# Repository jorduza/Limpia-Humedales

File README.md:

### Link a la wiki para la documentacion del trabajo
https://github.com/jorduza/Limpia-Humedales/wiki/0.-HOME

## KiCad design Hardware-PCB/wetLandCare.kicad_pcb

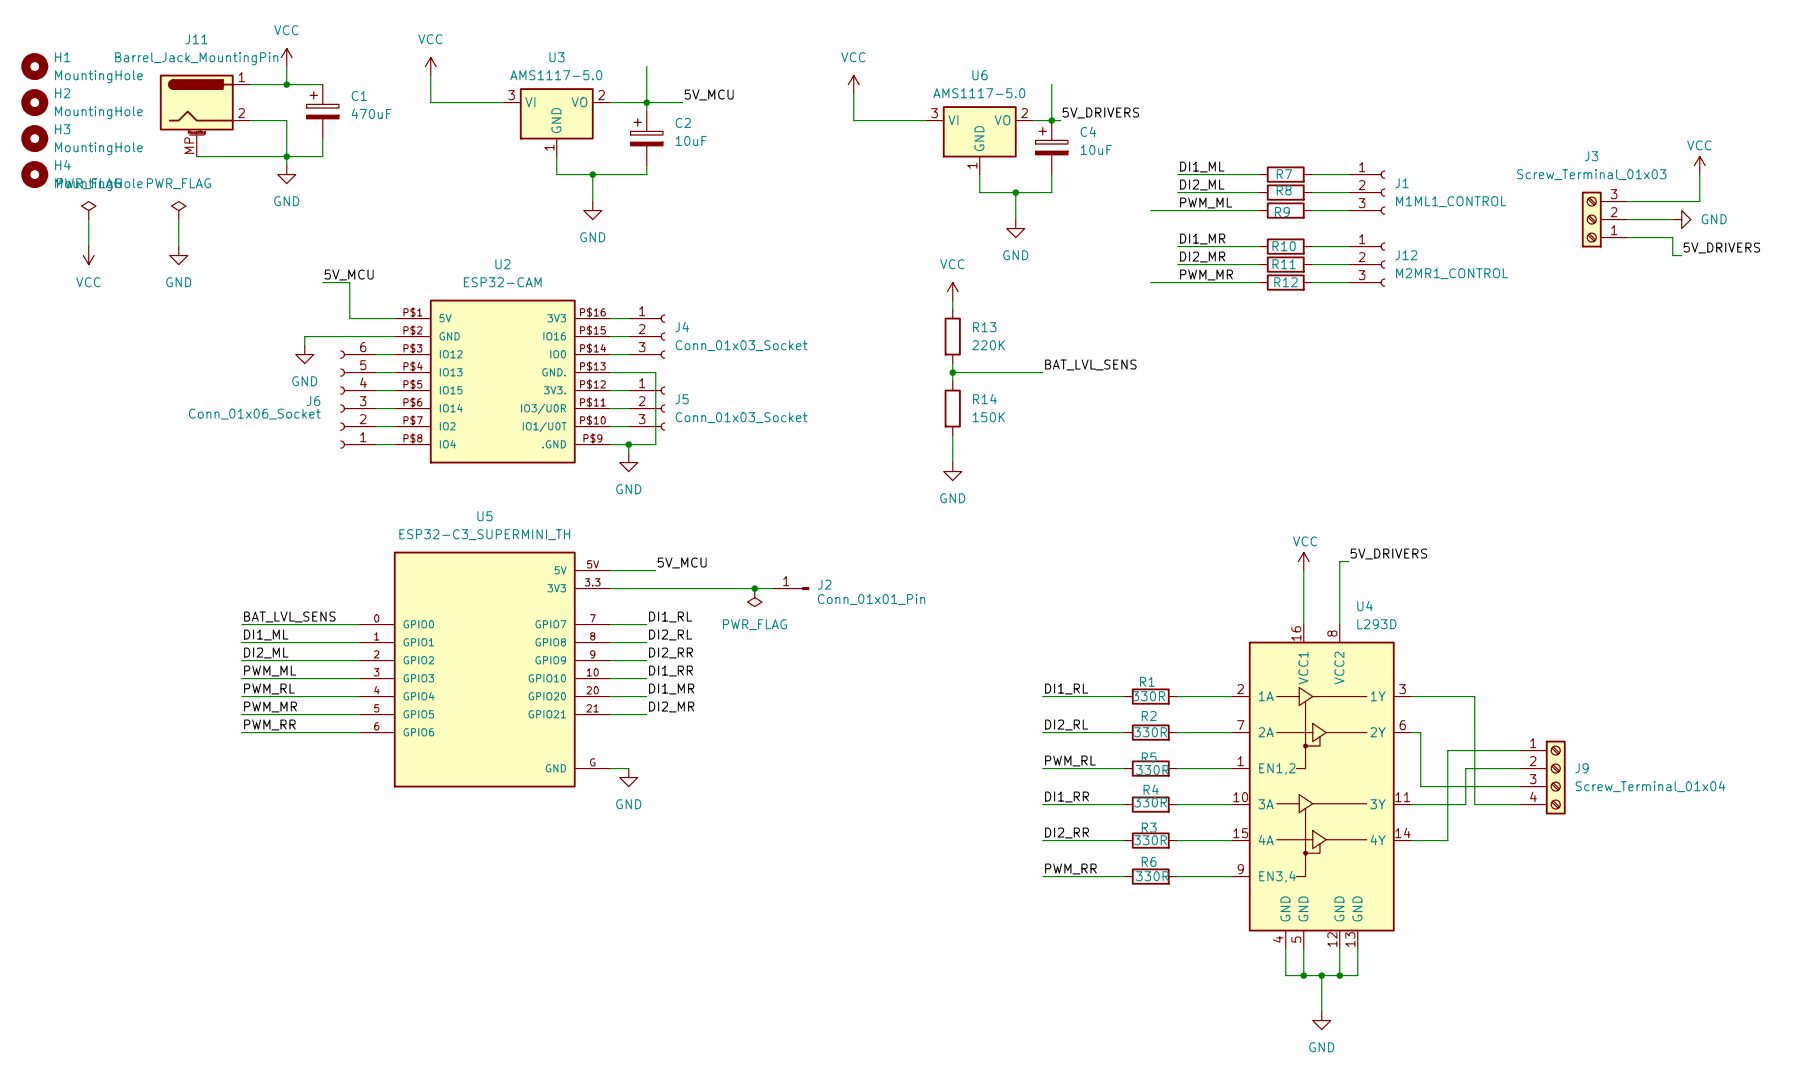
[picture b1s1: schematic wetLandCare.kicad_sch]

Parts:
C1: 470uF; CP_Radial_D8.0mm_P3.80mm
C2, C4: 10uF; CP_Radial_D4.0mm_P2.00mm
H1, H2, H3, H4: MountingHole; MountingHole_3.2mm_M3_DIN965_Pad
J1: M1ML1_CONTROL; PinSocket_1x03_P2.54mm_Vertical
J2: Conn_01x01_Pin; PinSocket_1x01_P2.54mm_Vertical
J3: Screw_Terminal_01x03; TerminalBlock_Altech_AK300-3_P5.00mm
J4, J5: Conn_01x03_Socket; PinSocket_1x03_P2.54mm_Vertical
J6: Conn_01x06_Socket; PinSocket_1x06_P2.54mm_Vertical
J9: Screw_Terminal_01x04; TerminalBlock_Altech_AK300-4_P5.00mm
J11: Barrel_Jack_MountingPin; BarrelJack_Kycon_KLDX-0202-xC_Horizontal
J12: M2MR1_CONTROL; PinSocket_1x03_P2.54mm_Vertical
R1, R2, R3, R4, R5, R6, R7, R8, R9, R10, R11, R12: 330R; R_Axial_DIN0207_L6.3mm_D2.5mm_P7.62mm_Horizontal
R13: 220K; R_Axial_DIN0207_L6.3mm_D2.5mm_P7.62mm_Horizontal
R14: 150K; R_Axial_DIN0207_L6.3mm_D2.5mm_P7.62mm_Horizontal
U2: ESP32-CAM
U3, U6: AMS1117-5.0; SOT-223-3_TabPin2
U4: L293D; DIP-16_W7.62mm
U5: ESP32-C3_SUPERMINI_TH; MODULE_ESP32-C3_SUPERMINI_TH

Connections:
/5V_DRIVERS: C4.1, J3.1, U4.8 (VCC2), U6.2 (VO)
/5V_MCU: C2.1, U2.P$1 (5V), U3.2 (VO), U5.5V
/BAT_LVL_SENS: R13.2, R14.1, U5.0 (GPIO0)
/DI1_ML: R7.1, U5.1 (GPIO1)
/DI1_MR: R10.1, U5.20 (GPIO20)
/DI1_RL: R1.1, U5.7 (GPIO7)
/DI1_RR: R4.1, U5.10 (GPIO10)
/DI2_ML: R8.1, U5.2 (GPIO2)
/DI2_MR: R11.1, U5.21 (GPIO21)
/DI2_RL: R2.1, U5.8 (GPIO8)
/DI2_RR: R3.1, U5.9 (GPIO9)
/PWM_ML: R9.1, U5.3 (GPIO3)
/PWM_MR: R12.1, U5.5 (GPIO5)
/PWM_RL: R5.1, U5.4 (GPIO4)
/PWM_RR: R6.1, U5.6 (GPIO6)
GND: C1.2, C2.2, C4.2, J3.2, J11.2, J11.MP, R14.2, U2.P$2 (GND), U2.P$9 (.GND), U2.P$13 (GND.), U3.1 (GND), U4.4 (GND), U4.5 (GND), U4.12 (GND), U4.13 (GND), U5.G (GND), U6.1 (GND)
unnamed: J1.1, R7.2
unnamed: J1.2, R8.2
unnamed: J1.3, R9.2
unnamed: J2.1, U5.3.3 (3V3)
unnamed: J4.1, U2.P$16 (3V3)
unnamed: J4.2, U2.P$15 (IO16)
unnamed: J4.3, U2.P$14 (IO0)
unnamed: J5.1, U2.P$12 (3V3.)
unnamed: J5.2, U2.P$11 (IO3/U0R)
unnamed: J5.3, U2.P$10 (IO1/U0T)
unnamed: J6.1, U2.P$8 (IO4)
unnamed: J6.2, U2.P$7 (IO2)
unnamed: J6.3, U2.P$6 (IO14)
unnamed: J6.4, U2.P$5 (IO15)
unnamed: J6.5, U2.P$4 (IO13)
unnamed: J6.6, U2.P$3 (IO12)
unnamed: J9.1, U4.14 (4Y)
unnamed: J9.2, U4.11 (3Y)
unnamed: J9.3, U4.6 (2Y)
unnamed: J9.4, U4.3 (1Y)
unnamed: J12.1, R10.2
unnamed: J12.2, R11.2
unnamed: J12.3, R12.2
unnamed: R1.2, U4.2 (1A)
unnamed: R2.2, U4.7 (2A)
unnamed: R4.2, U4.10 (3A)
unnamed: R3.2, U4.15 (4A)
unnamed: R5.2, U4.1 (EN1,2)
unnamed: R6.2, U4.9 (EN3,4)
VCC: C1.1, J3.3, J11.1, R13.1, U3.3 (VI), U4.16 (VCC1), U6.3 (VI)

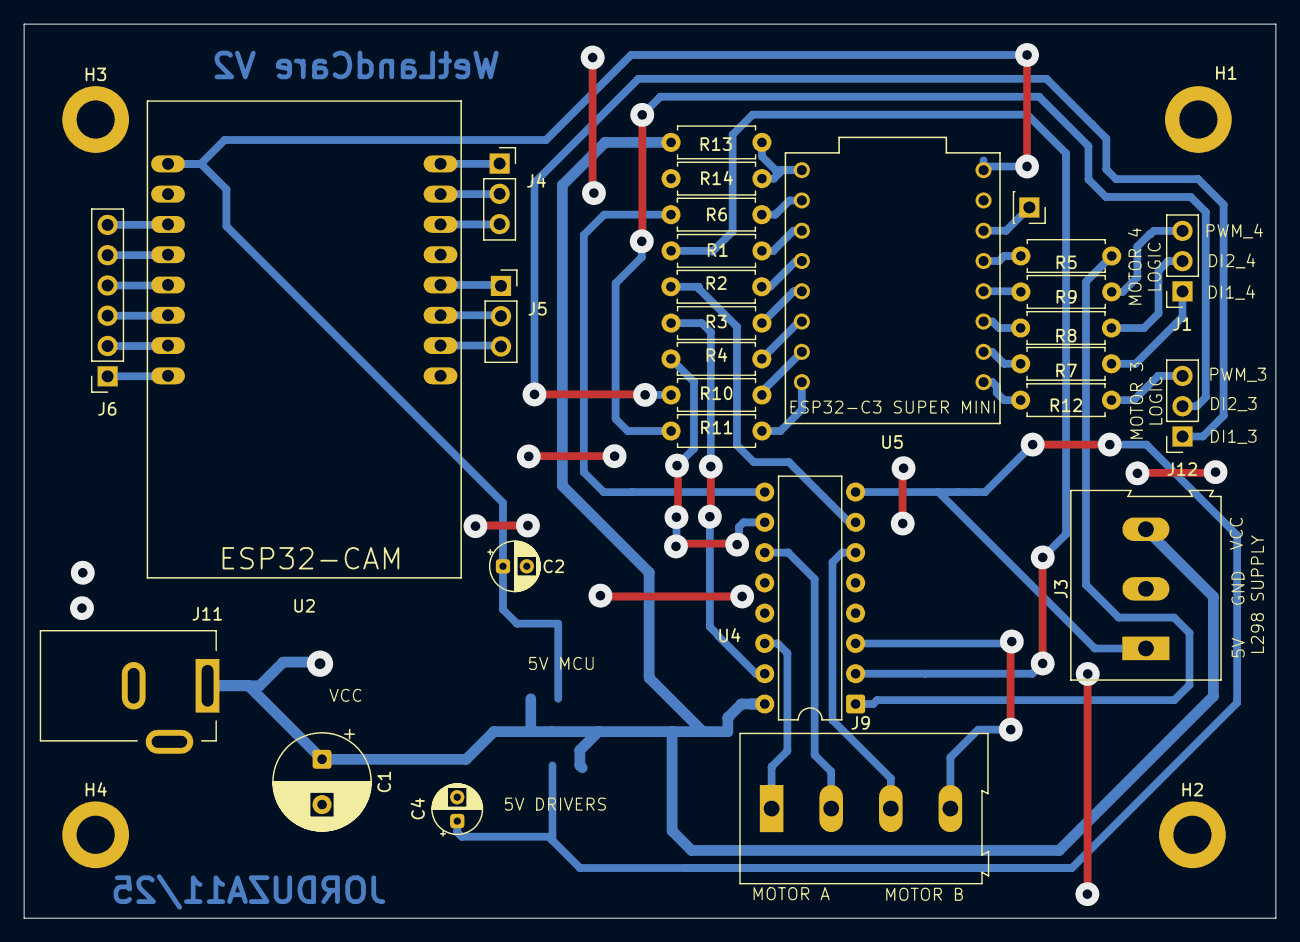
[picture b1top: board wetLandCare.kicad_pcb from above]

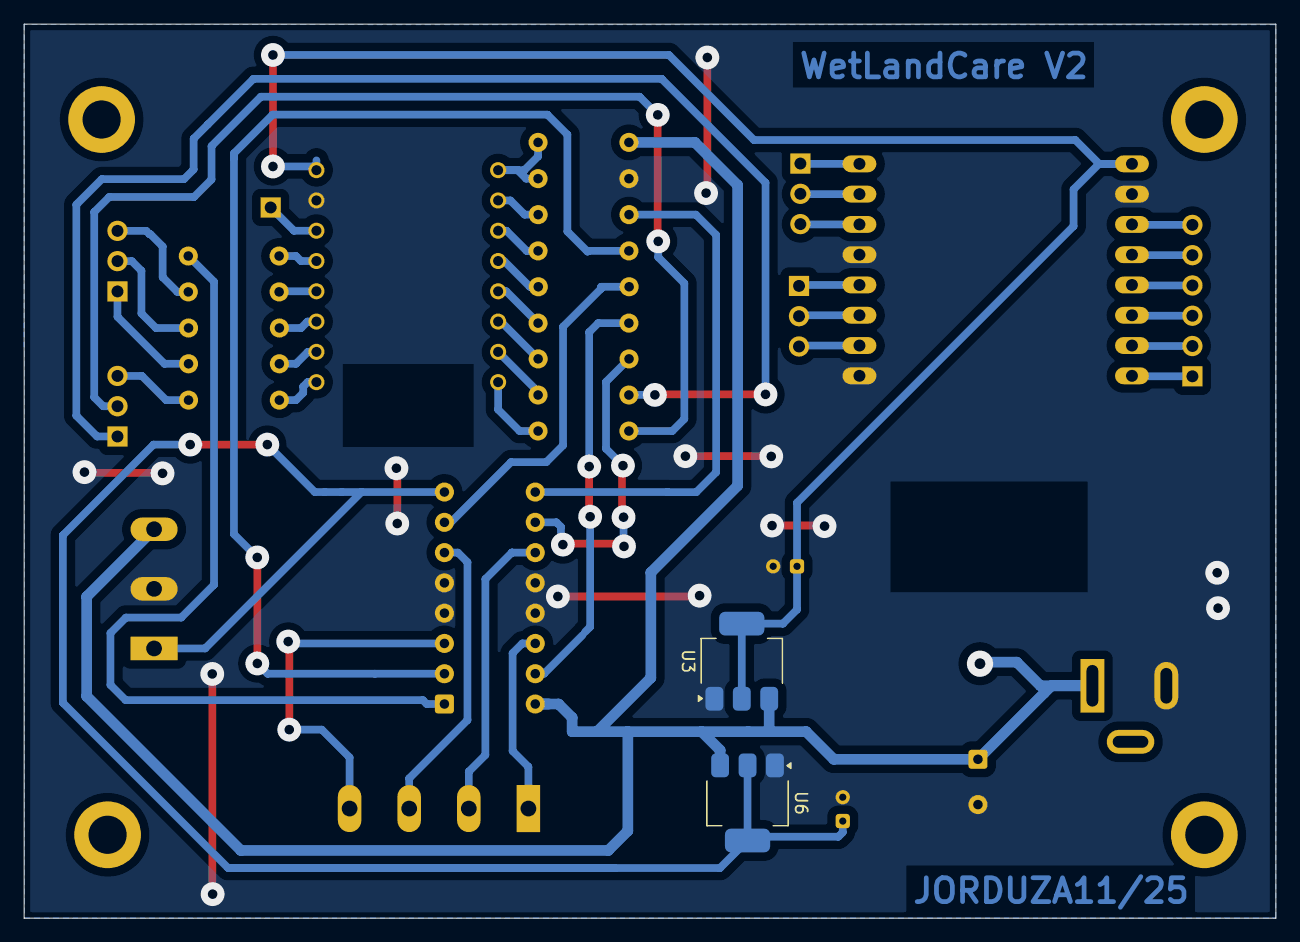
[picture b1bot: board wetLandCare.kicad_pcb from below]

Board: 2 copper layers, 105.0 x 75.0 mm, 35 parts (2 on the bottom side), 46 nets.

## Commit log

2025-10-22 Create diagram
2025-10-23 Add collaborator guidelines to README
    Added a section for collaborators to the README.
2025-10-25 Fix formatting in README for collaborators section
2025-10-26 Rename Diseño sin título.png to DF Interaccion HM.png
2025-11-12 Add files via upload
    Dathasheets de los componentes usados en el proyecto
2025-11-12 Add files via upload
    Modificación y complementación del diagrama esquemático como parte del diseño técnico del prototipo
2025-11-15 added via upload
    Modificaciones al esquemático y diseño del circuito impreso
2025-12-09 updated kicad files
2025-12-12 Add space after '###' in README.md
2025-12-12 DIAGRAMA TECNOLOGICO
